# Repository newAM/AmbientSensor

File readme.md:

## Ambient Sensor

### What is it?
This project is a ambient environment sensor that gathers the luminosity, temperature, humidity, and pressure.  This data is transmitted in real time to my Home Assistant server via MQTT over Ethernet.

### Why?
I wanted to explore real-time adjustments of lighting, and window coverings to maintain constant light levels in a room, which requires high sample rates (multiple samples per second) for responsive adjustments.

When I started this project there were no high-sample rate luminosity sensors for home automation.  The devices that did exist either had low sample rates (minutes vs milliseconds), or were designed for scientific applications.

### Project Contents
* AmbientSensor_Code - firmware source code
* AmbientSensor_HomeAssisant - sample configuration for use with HomeAssistant
* AmbientSensor_KiCAD - schematic and PCB
* AmbientSensor_Peripheral - schematic and PCB for peripheral sensors
* AmbientSensor_Media - photos

### Prototype and Design
See [prototyping.md](prototyping.md) for the prototyping and design process.

### Software Used
* KiCAD 5.0.2
* GNU Make 4.1
* GNU gdb (GNU Tools for Arm Embedded Processors 7-2018-q3-update) 8.1.0.20180315
* GNU gcc (GNU Tools for Arm Embedded Processors 7-2018-q3-update) 7.3.1 20180622
* STM32CubeMX 5.1.0
* OpenOCD 0.10.0

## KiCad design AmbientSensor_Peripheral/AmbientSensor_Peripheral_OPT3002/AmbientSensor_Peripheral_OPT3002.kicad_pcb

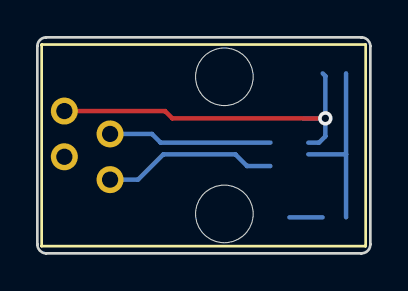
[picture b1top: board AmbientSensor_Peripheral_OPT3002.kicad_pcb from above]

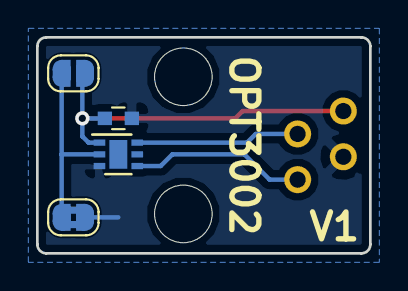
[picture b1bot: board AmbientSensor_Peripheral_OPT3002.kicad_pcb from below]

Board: 2 copper layers, 18.5 x 12.0 mm, 5 parts (4 on the bottom side), 5 nets.

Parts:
C1: 100u; C_0603
J1: NO; SolderJumper-2_P1.3mm_Open_RoundedPad1.0x1.5mm
J2: NC; SolderJumper-2_P1.3mm_Bridged2Bar_RoundedPad1.0x1.5mm
U1: OPT3002; DFN-6-1EP_2x2mm_Pitch0.65mm
X1: RJ22; A-2004-3-4-LP-N-R

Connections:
+3V3: C1.1, J1.1, U1.1, X1.4
GND: C1.2, J2.1, U1.3, X1.2
unnamed: J1.2, J2.2, U1.2
SCL: U1.4, X1.1
SDA: U1.6, X1.3

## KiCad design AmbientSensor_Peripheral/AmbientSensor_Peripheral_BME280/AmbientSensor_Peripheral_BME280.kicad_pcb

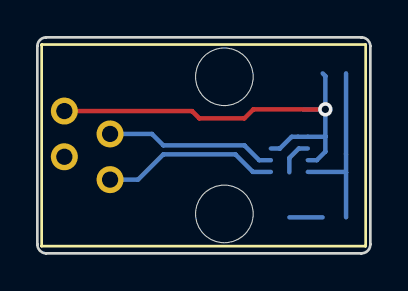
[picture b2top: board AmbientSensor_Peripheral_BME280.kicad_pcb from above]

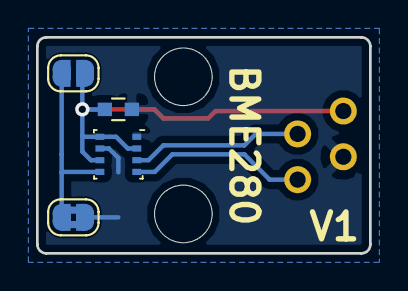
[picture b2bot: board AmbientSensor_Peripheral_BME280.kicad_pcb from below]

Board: 2 copper layers, 18.5 x 12.0 mm, 5 parts (4 on the bottom side), 5 nets.

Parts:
C1: 100u; C_0603
J1: NO; SolderJumper-2_P1.3mm_Open_RoundedPad1.0x1.5mm
J2: NC; SolderJumper-2_P1.3mm_Bridged2Bar_RoundedPad1.0x1.5mm
U1: BME280; Bosch_LGA-8_2.5x2.5mm_Pitch0.65mm_ClockwisePinNumbering
X1: RJ22; A-2004-3-4-LP-N-R

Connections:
+3V3: C1.1, J1.1, U1.2, U1.6, U1.8, X1.4
GND: C1.2, J2.1, U1.1, U1.7, X1.2
unnamed: J1.2, J2.2, U1.5
SCL: U1.4, X1.1
SDA: U1.3, X1.3

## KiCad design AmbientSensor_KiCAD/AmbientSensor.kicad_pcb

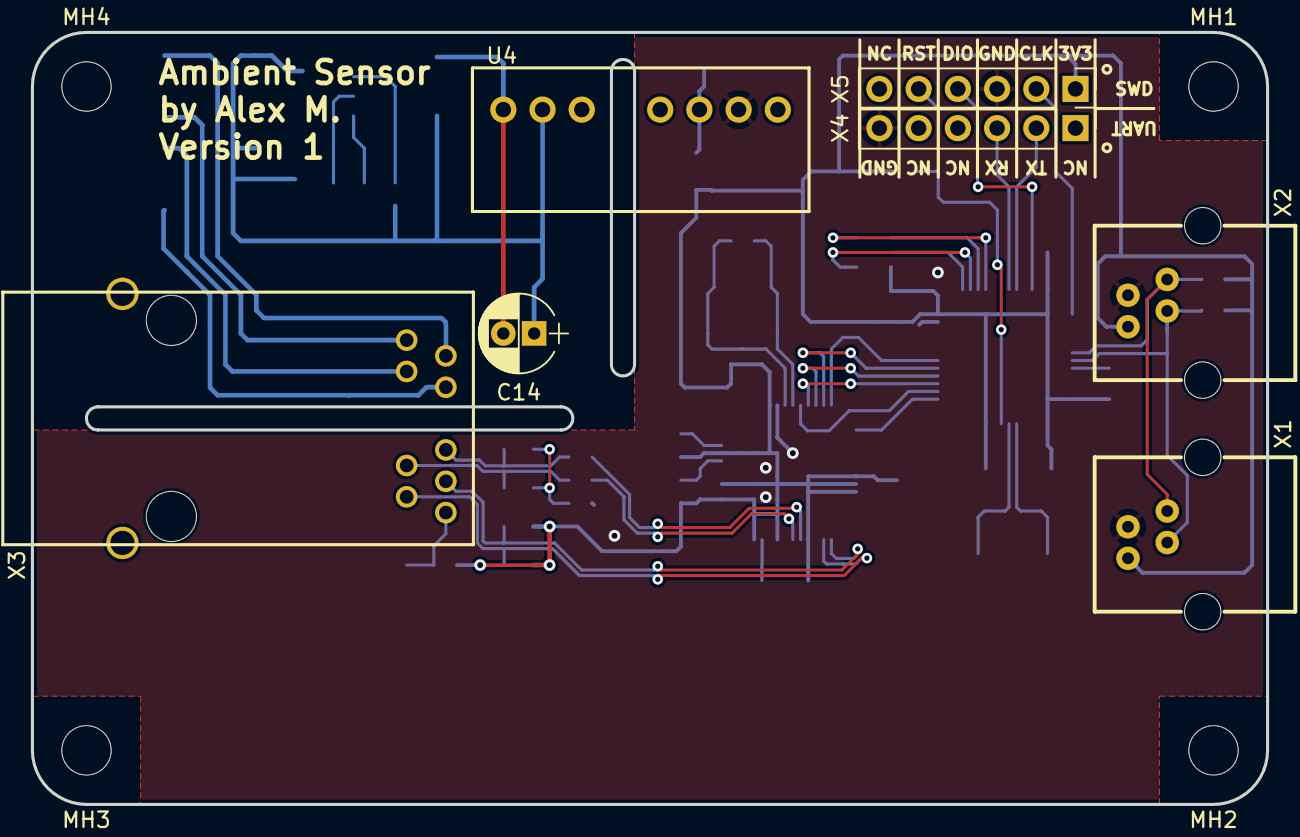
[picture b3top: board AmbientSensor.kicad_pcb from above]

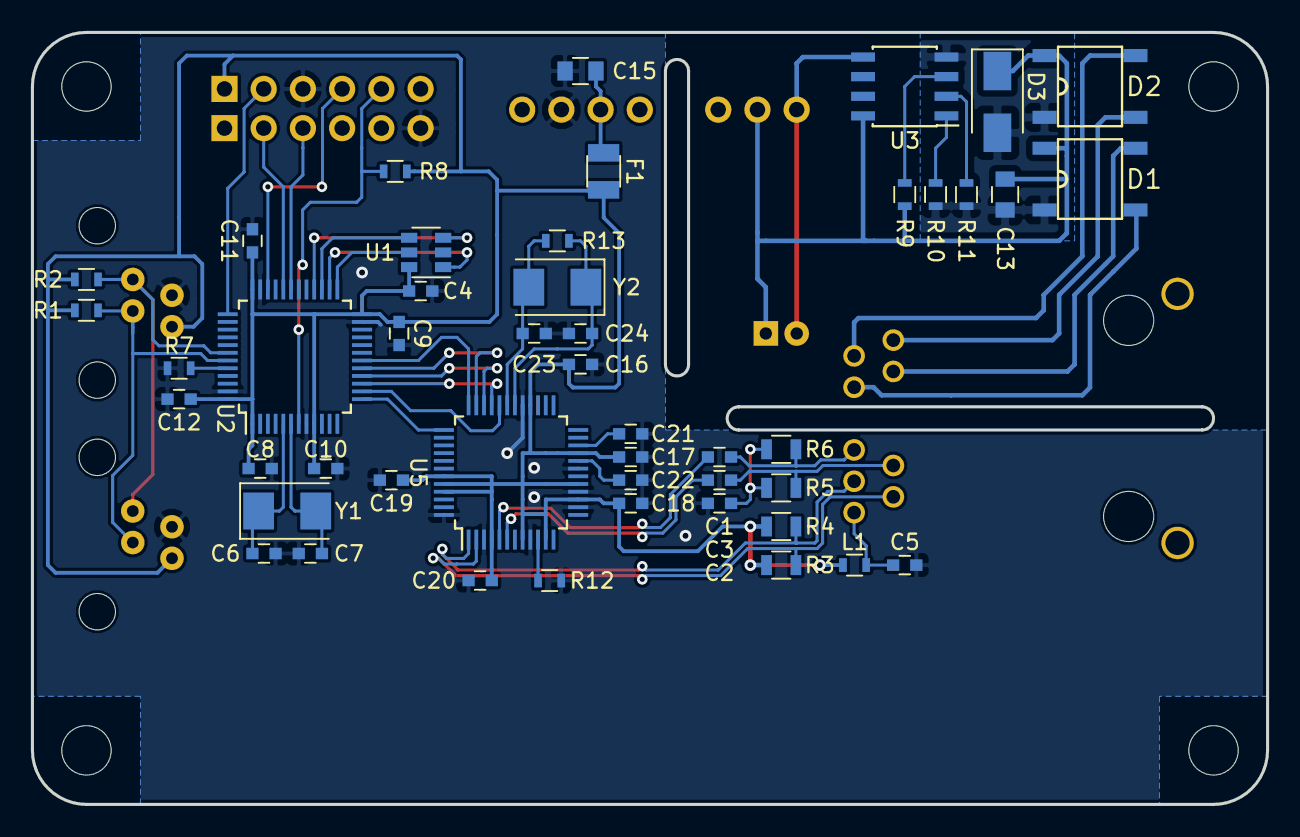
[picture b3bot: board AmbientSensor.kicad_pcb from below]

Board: 2 copper layers, 80.0 x 50.0 mm, 58 parts (47 on the bottom side), 46 nets.

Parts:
C1, C3, C21: 10n; C_0603
C2, C4, C5, C8, C9, C10, C11, C12, C16, C17, C18, C19, C20: 100n; C_0603
C6, C7, C23, C24: 18p; C_0603
C13: 100n; C_0805
C14: 22u; CP_Radial_D5.0mm_P2.00mm
C15: 10u; C_0805
C22: 4.7u; C_0603
D1, D2: MDB6S; Micro-DIP-4
D3: SMAJ58A; D_SMA
F1: 500m; Fuse_SMD1206_Reflow
L1: 1u; L_0603
MH1, MH2, MH3, MH4: MountingHole; MountingHole_3.2mm_M3
R1, R2, R7, R8: 4.7k; R_0603
R3, R4, R5, R6: 49.9; R_0805
R9: 24.9k; R_0603
R10: 178k; R_0603
R11: 4420; R_0603
R12: 12.4k; R_0603
R13: 1M; R_0603
U1: 25AA02E48T-I_OT; SOT-23-6
U2: STM32F070CBTx; LQFP-48_7x7mm_Pitch0.5mm
U3: NCP1090; SOIC-8_3.9x4.9mm_Pitch1.27mm
U4: PG02S4803A; PG02S
U5: W5500; LQFP-48_7x7mm_Pitch0.5mm
X1, X2: 4P4C; E5544-60LU22-L
X3: 0813-1X1T-57-F; 0813-1X1T-57-F_RJ45-Jack
X4: USART; Pin_Header_Straight_1x06_Pitch2.54mm
X5: JTAG; Pin_Header_Straight_1x06_Pitch2.54mm
Y1: 8M; Crystal_SMD_5032-2pin_5.0x3.2mm
Y2: 25MHz; Crystal_SMD_5032-2pin_5.0x3.2mm

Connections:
+3V3: C4.1, C8.1, C9.1, C10.1, C11.1, C12.1, C16.1, C17.1, C18.1, C19.1, C20.1, F1.2, L1.1, R1.1, R2.1, R3.1, R4.1, R8.1, U1.6, U2.1, U2.9, U2.24, U2.36, U2.48, U5.4, U5.8, U5.11, U5.15, U5.17, U5.21, U5.28, U5.43, U5.44, U5.45, X1.4, X2.4, X5.1
/CRXIN: C1.2, R6.2, X3.9
/CRXIP: C3.2, R5.2, X3.2
/PoE PD Interface/3.3V: C15.1, F1.1, U4.6
/PoE PD Interface/N: C13.2, D1.2, D2.2, D3.2, R10.1, R11.1, U3.4
/PoE PD Interface/P: C13.1, C14.1, D1.1, D2.1, D3.1, R9.2, U3.8, U4.2
/PoE PD Interface/VC12: D1.4, X3.5
/PoE PD Interface/VC36: D1.3, X3.10
/PoE PD Interface/VC45: D2.3, X3.6
/PoE PD Interface/VC78: D2.4, X3.11
/W5500 Ethernet Interface/1V2O: C21.1, U5.22
/W5500 Ethernet Interface/RXIN: C1.1, U5.5
/W5500 Ethernet Interface/RXIP: C3.1, U5.6
/W5500 Ethernet Interface/TXON: R4.2, U5.1, X3.8
/W5500 Ethernet Interface/TXOP: R3.2, U5.2, X3.1
/W5500 Ethernet Interface/XCAP: C22.1, U5.20
/W5500 Ethernet Interface/XI: C24.1, R13.1, U5.30, Y2.1
/W5500 Ethernet Interface/XO: C23.1, R13.2, U5.31, Y2.2
/W5500 Ethernet Interface/XRES: R12.1, U5.10
GND: C2.2, C4.2, C5.2, C6.2, C7.2, C8.2, C9.2, C10.2, C11.2, C12.2, C15.2, C16.2, C17.2, C18.2, C19.2, C20.2, C21.2, C22.2, C23.2, C24.2, R7.1, R12.2, U1.2, U2.8, U2.23, U2.35, U2.47, U4.7, U5.3, U5.9, U5.14, U5.16, U5.19, U5.29, U5.48, X1.2, X2.2, X4.6, X5.3
I2C1_SCL: R2.2, U2.42, X1.1, X2.1
I2C1_SDA: R1.2, U2.43, X1.3, X2.3
NRST: R8.2, U2.7, X5.5
unnamed: C2.1, R5.1, R6.1
unnamed: C5.1, L1.2, X3.7
unnamed: C6.1, U2.5, Y1.1
unnamed: C7.1, U2.6, Y1.2
unnamed: C14.2, U3.5, U4.1
unnamed: R7.2, U2.44
unnamed: R9.1, U3.3
unnamed: R10.2, U3.1
unnamed: R11.2, U3.2
SP1_MOSI: U2.17, U5.35
SPI1_MISO: U2.16, U5.34
SPI1_NSS: U2.14, U5.32
SPI1_SCK: U2.15, U5.33
SPI2_MISO: U1.4, U2.27
SPI2_MOSI: U1.3, U2.28
SPI2_NSS: U1.5, U2.25
SPI2_SCK: U1.1, U2.26
SYS_SWCLK: U2.37, X5.2
SYS_SWDIO: U2.34, X5.4
USART1_RX: U2.31, X4.3
USART1_TX: U2.32, X4.2
WIZ_INT: U2.18, U5.36
WIZ_RST: U2.13, U5.37

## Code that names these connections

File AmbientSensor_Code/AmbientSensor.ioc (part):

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Mcu.Name=STM32F070CBTx
Mcu.Package=LQFP48
Mcu.UserName=STM32F070CBTx
PA10.Mode=Asynchronous
PA10.Signal=USART1_RX
PA13.Mode=Serial_Wire
PA13.Signal=SYS_SWDIO
PA14.Mode=Serial_Wire
PA14.Signal=SYS_SWCLK
PA3.GPIOParameters=GPIO_Label
PA3.GPIO_Label=WIZ_RST
PA3.Signal=GPIO_Output
PA4.GPIOParameters=PinState,GPIO_Label
PA4.GPIO_Label=WIZ_CS
PA4.PinState=GPIO_PIN_SET
PA4.Signal=GPIO_Output
PA5.Mode=Full_Duplex_Master
PA5.Signal=SPI1_SCK
PA6.Mode=Full_Duplex_Master
PA6.Signal=SPI1_MISO
PA7.Mode=Full_Duplex_Master
PA7.Signal=SPI1_MOSI
PA9.Mode=Asynchronous
PA9.Signal=USART1_TX
PB0.GPIOParameters=GPIO_Label,GPIO_ModeDefaultEXTI
PB0.GPIO_Label=WIZ_INT
PB0.GPIO_ModeDefaultEXTI=GPIO_MODE_IT_FALLING
PB0.Signal=GPXTI0
PB12.GPIOParameters=PinState,GPIO_Label
PB12.GPIO_Label=EEPROM_CS
PB12.PinState=GPIO_PIN_SET
PB12.Signal=GPIO_Output
PB13.Mode=Full_Duplex_Master
PB13.Signal=SPI2_SCK
PB14.Mode=Full_Duplex_Master
PB14.Signal=SPI2_MISO
PB15.Mode=Full_Duplex_Master
PB15.Signal=SPI2_MOSI
PB6.Mode=I2C
PB6.Signal=I2C1_SCL
PB7.Mode=I2C
PB7.Signal=I2C1_SDA
PF0-OSC_IN.Mode=HSE-External-Oscillator
PF0-OSC_IN.Signal=RCC_OSC_IN
PF1-OSC_OUT.Mode=HSE-External-Oscillator
PF1-OSC_OUT.Signal=RCC_OSC_OUT
board=custom

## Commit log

2019-06-01 Initial Commit.
